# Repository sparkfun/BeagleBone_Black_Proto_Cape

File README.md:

BeagleBone Black Proto Cape
===========================

[
*BeagleBone Black Proto Cape (DEV-12774)*](https://www.sparkfun.com/products/12774)
 
 A prototyping cape designed for the BeagleBone Black. It has blank EEPROM for pin configuration data and
 two red LEDs for debugging. 

Repository Contents
-------------------
* **/Hardware** - All Eagle design files (.brd, .sch, .STL)
* **/Production** - Test bed files and production panel files

Version History
---------------
* [V_1.0.0](https://github.com/sparkfun/BeagleBone_Black_Proto_Cape/tree/V_1.0.0) - Public release
* [V_1.0.1](https://github.com/sparkfun/BeagleBone_Black_Proto_Cape/tree/V_1.0.1) - Updated jumper packages to DFM standard (Increased aperture).

License Information
-------------------
The hardware is released under [Creative Commons ShareAlike 4.0 International](https://creativecommons.org/licenses/by-sa/4.0/).
The code is beerware; if you see me (or any other SparkFun employee) at the local, and you've found our code helpful, please buy us a round!

Distributed as-is; no warranty is given.

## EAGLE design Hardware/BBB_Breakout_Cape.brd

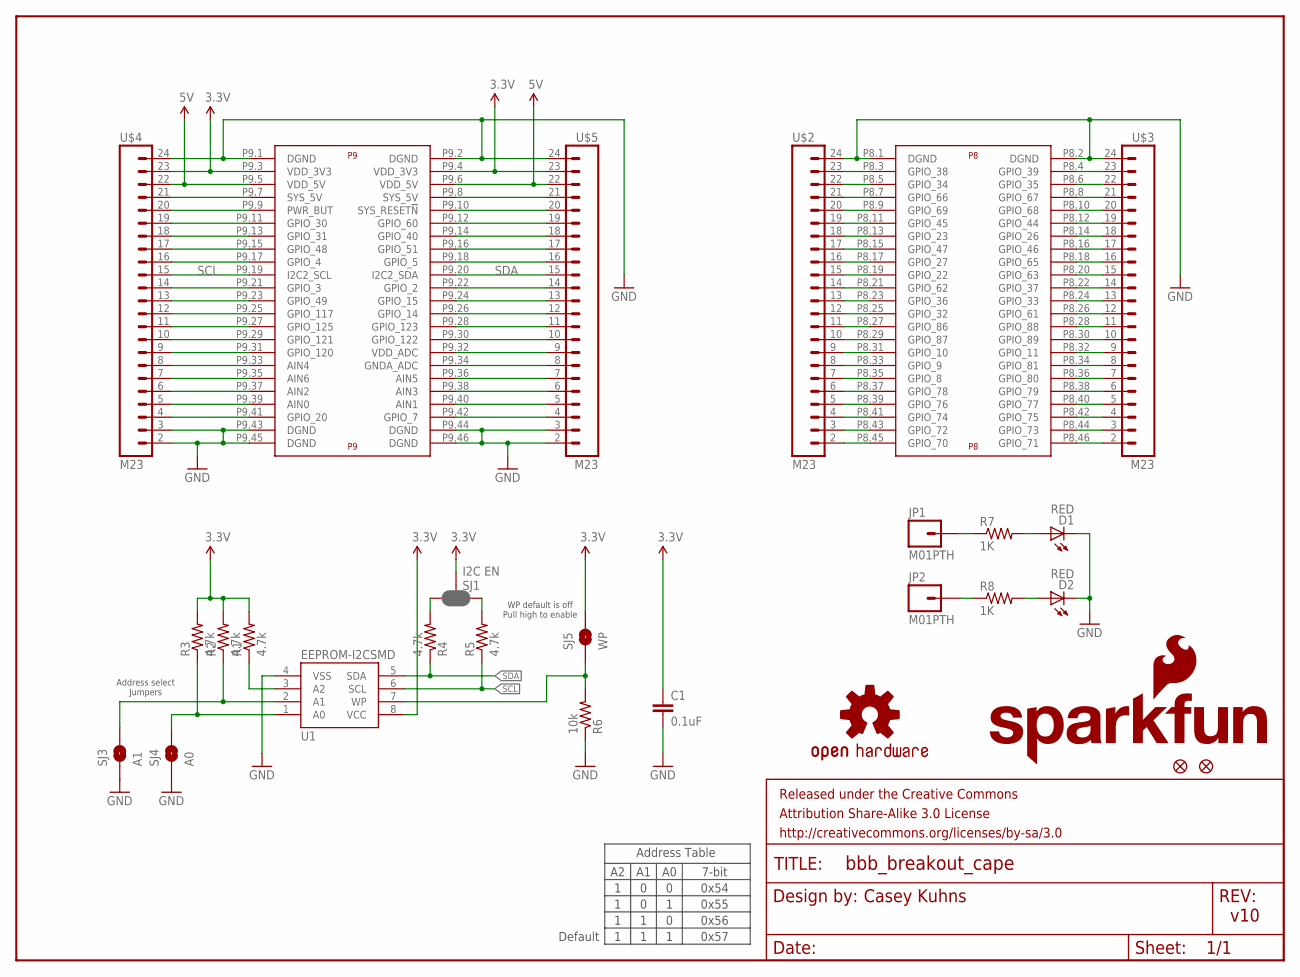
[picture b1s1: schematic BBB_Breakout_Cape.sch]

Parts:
C1: 0.1uF; 0603-CAP
D1, D2: RED; LED-0603
FID1, FID2: FIDUCIAL1X2; FIDUCIAL-1X2
FRAME1: FRAME-LETTER; CREATIVE_COMMONS
JP1, JP2: M01PTH; 1X01
LOGO2: OSHW-LOGOS; OSHW-LOGO-S
LOGO3: SFE_LOGO_NAME_FLAME.1_INCH; SFE_LOGO_NAME_FLAME_.1
R1, R2, R3, R4, R5: 4.7k; 0603@1
R6: 10k; 0603-RES
R7, R8: 1K; 0603-RES
SJ1: I2C EN; SMT-JUMPER_3_2-NC_PASTE_SILK
SJ3: A1; SMT-JUMPER_2_NO_SILK
SJ4: A0; SMT-JUMPER_2_NO_SILK
SJ5: WP; SMT-JUMPER_2_NO_SILK
U1: EEPROM-I2CSMD; SO08
U$1: BEAGLE_BONE_BLACK_CAPE
U$2, U$3, U$4, U$5: M23; 1X23

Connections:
3.3V: C1.1, R1.2, R2.2, R3.2, SJ1.2, SJ5.2, U1.8 (VCC), U$1.P9.3 (VDD_3V3), U$1.P9.4 (VDD_3V3), U$4.23, U$5.23
5V: U$1.P9.5 (VDD_5V), U$1.P9.6 (VDD_5V), U$4.22, U$5.22
A0: R3.1, SJ4.2, U1.1 (A0)
A1: R2.1, SJ3.2, U1.2 (A1)
GND: C1.2, D1.C, D2.C, R6.1, SJ3.1, SJ4.1, U1.4 (VSS), U$1.P8.1 (DGND), U$1.P8.2 (DGND), U$1.P9.1 (DGND), U$1.P9.2 (DGND), U$1.P9.43 (DGND), U$1.P9.44 (DGND), U$1.P9.45 (DGND), U$1.P9.46 (DGND), U$2.24, U$3.24, U$4.2, U$4.3, U$4.24, U$5.2, U$5.3, U$5.24
unnamed: R6.2, SJ5.1, U1.7 (WP)
unnamed: U$1.P8.45 (GPIO_70), U$2.2
unnamed: D1.A, R7.2
unnamed: U$1.P8.43 (GPIO_72), U$2.3
unnamed: U$1.P8.41 (GPIO_74), U$2.4
unnamed: R1.1, U1.3 (A2)
unnamed: D2.A, R8.2
unnamed: JP1.1, R7.1
unnamed: U$1.P8.39 (GPIO_76), U$2.5
unnamed: R4.2, SJ1.3
unnamed: R5.2, SJ1.1
unnamed: U$1.P8.37 (GPIO_78), U$2.6
unnamed: U$1.P8.35 (GPIO_8), U$2.7
unnamed: U$1.P8.33 (GPIO_9), U$2.8
unnamed: U$1.P8.31 (GPIO_10), U$2.9
unnamed: U$1.P8.29 (GPIO_87), U$2.10
unnamed: U$1.P8.27 (GPIO_86), U$2.11
unnamed: U$1.P8.25 (GPIO_32), U$2.12
unnamed: U$1.P8.23 (GPIO_36), U$2.13
unnamed: U$1.P8.21 (GPIO_62), U$2.14
unnamed: U$1.P8.19 (GPIO_22), U$2.15
unnamed: U$1.P8.17 (GPIO_27), U$2.16
unnamed: U$1.P8.15 (GPIO_47), U$2.17
unnamed: U$1.P8.13 (GPIO_23), U$2.18
unnamed: U$1.P8.11 (GPIO_45), U$2.19
unnamed: U$1.P8.9 (GPIO_69), U$2.20
unnamed: U$1.P8.7 (GPIO_66), U$2.21
unnamed: U$1.P8.5 (GPIO_34), U$2.22
unnamed: U$1.P8.3 (GPIO_38), U$2.23
unnamed: JP2.1, R8.1
unnamed: U$1.P8.46 (GPIO_71), U$3.2
unnamed: U$1.P8.44 (GPIO_73), U$3.3
unnamed: U$1.P8.42 (GPIO_75), U$3.4
unnamed: U$1.P8.40 (GPIO_77), U$3.5
unnamed: U$1.P8.38 (GPIO_79), U$3.6
unnamed: U$1.P8.36 (GPIO_80), U$3.7
unnamed: U$1.P8.34 (GPIO_81), U$3.8
unnamed: U$1.P8.32 (GPIO_11), U$3.9
unnamed: U$1.P8.30 (GPIO_89), U$3.10
unnamed: U$1.P8.28 (GPIO_88), U$3.11
unnamed: U$1.P8.26 (GPIO_61), U$3.12
unnamed: U$1.P8.24 (GPIO_33), U$3.13
unnamed: U$1.P8.22 (GPIO_37), U$3.14
unnamed: U$1.P8.20 (GPIO_63), U$3.15
unnamed: U$1.P8.18 (GPIO_65), U$3.16
unnamed: U$1.P8.16 (GPIO_46), U$3.17
unnamed: U$1.P8.14 (GPIO_26), U$3.18
unnamed: U$1.P8.12 (GPIO_44), U$3.19
unnamed: U$1.P8.10 (GPIO_68), U$3.20
unnamed: U$1.P8.8 (GPIO_67), U$3.21
unnamed: U$1.P8.6 (GPIO_35), U$3.22
unnamed: U$1.P8.4 (GPIO_39), U$3.23
unnamed: U$1.P9.42 (GPIO_7), U$5.4
unnamed: U$1.P9.40 (AIN1), U$5.5
unnamed: U$1.P9.38 (AIN3), U$5.6
unnamed: U$1.P9.36 (AIN5), U$5.7
unnamed: U$1.P9.34 (GNDA_ADC), U$5.8
unnamed: U$1.P9.32 (VDD_ADC), U$5.9
unnamed: U$1.P9.30 (GPIO_122), U$5.10
unnamed: U$1.P9.28 (GPIO_123), U$5.11
unnamed: U$1.P9.26 (GPIO_14), U$5.12
unnamed: U$1.P9.24 (GPIO_15), U$5.13
unnamed: U$1.P9.22 (GPIO_2), U$5.14
unnamed: U$1.P9.18 (GPIO_5), U$5.16
unnamed: U$1.P9.16 (GPIO_51), U$5.17
unnamed: U$1.P9.14 (GPIO_40), U$5.18
unnamed: U$1.P9.12 (GPIO_60), U$5.19
unnamed: U$1.P9.10 (SYS_RESET!N), U$5.20
unnamed: U$1.P9.8 (SYS_5V), U$5.21
unnamed: U$1.P9.41 (GPIO_20), U$4.4
unnamed: U$1.P9.39 (AIN0), U$4.5
unnamed: U$1.P9.37 (AIN2), U$4.6
unnamed: U$1.P9.35 (AIN6), U$4.7
unnamed: U$1.P9.33 (AIN4), U$4.8
unnamed: U$1.P9.31 (GPIO_120), U$4.9
unnamed: U$1.P9.29 (GPIO_121), U$4.10
unnamed: U$1.P9.27 (GPIO_125), U$4.11
unnamed: U$1.P9.25 (GPIO_117), U$4.12
unnamed: U$1.P9.23 (GPIO_49), U$4.13
unnamed: U$1.P9.21 (GPIO_3), U$4.14
unnamed: U$1.P9.17 (GPIO_4), U$4.16
unnamed: U$1.P9.15 (GPIO_48), U$4.17
unnamed: U$1.P9.13 (GPIO_31), U$4.18
unnamed: U$1.P9.11 (GPIO_30), U$4.19
unnamed: U$1.P9.9 (PWR_BUT), U$4.20
unnamed: U$1.P9.7 (SYS_5V), U$4.21
SCL: R5.1, U1.6 (SCL), U$1.P9.19 (I2C2_SCL), U$4.15
SDA: R4.1, U1.5 (SDA), U$1.P9.20 (I2C2_SDA), U$5.15

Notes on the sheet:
Address Table
Default
7-bit
0x54
0x56
0x55
0x57
Casey Kuhns
v10
WP default is off Pull high to enable
Address select Jumpers

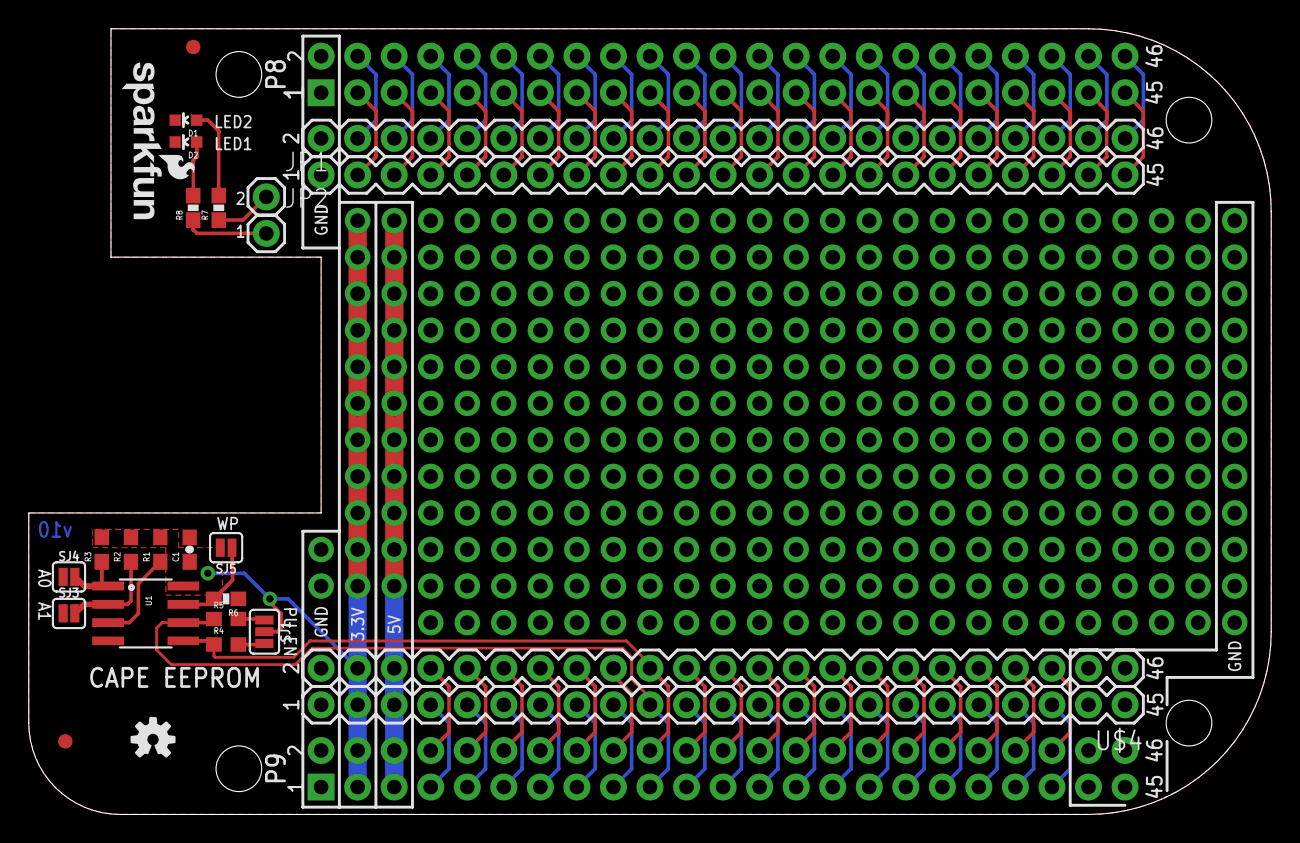
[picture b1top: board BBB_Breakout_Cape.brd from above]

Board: 2 copper layers, 86.4 x 54.6 mm, 29 parts (1 on the bottom side), 93 nets.

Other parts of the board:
U$6: SFE_LOGO_NAME_FLAME_.1

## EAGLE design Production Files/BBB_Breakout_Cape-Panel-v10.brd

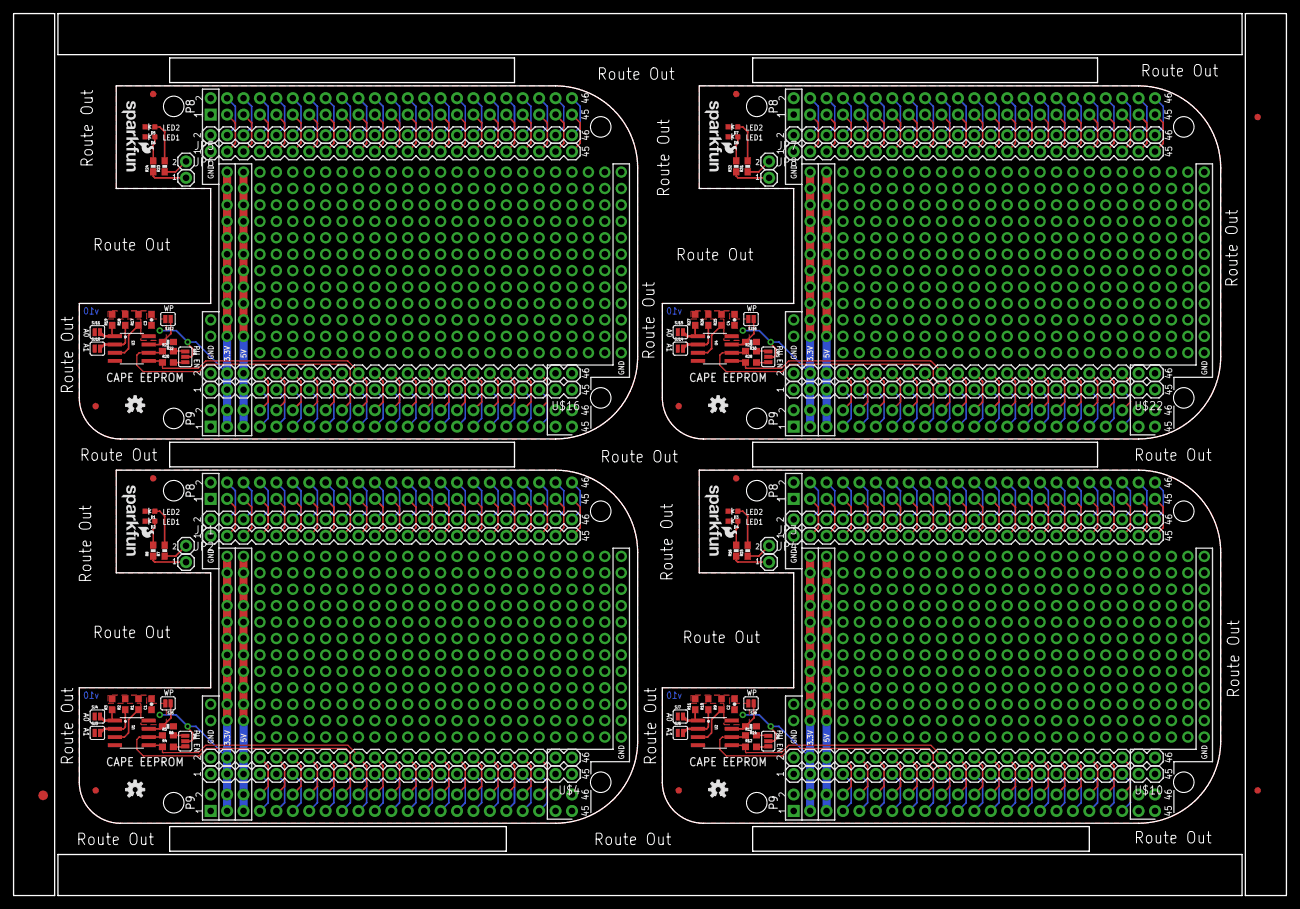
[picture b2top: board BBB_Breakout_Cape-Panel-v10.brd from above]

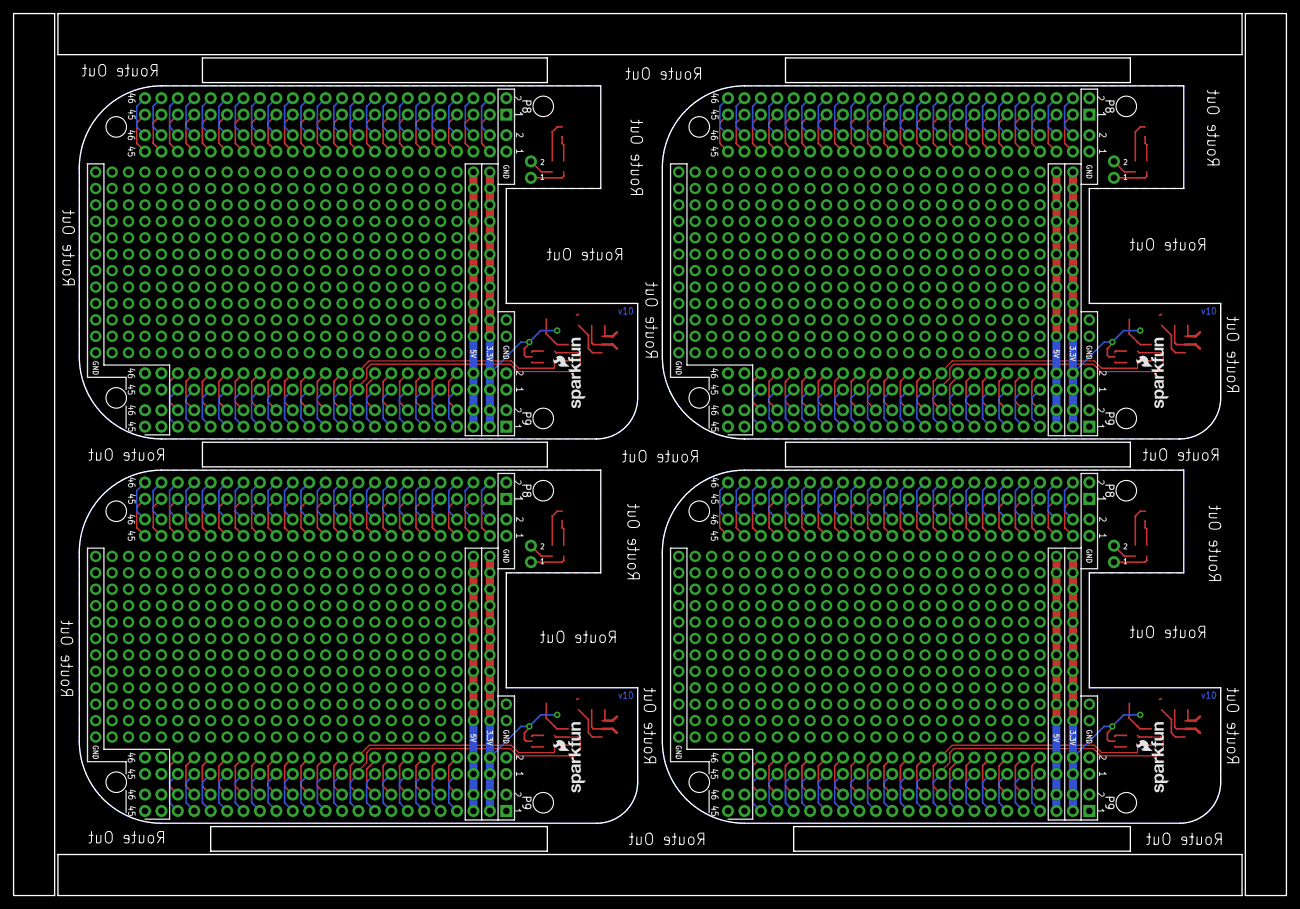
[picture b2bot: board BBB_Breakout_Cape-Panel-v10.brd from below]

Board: 2 copper layers, 196.8 x 136.4 mm, 115 parts (4 on the bottom side), 372 nets.

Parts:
C1, C2, C3, C4: 0.1uF; 0603-CAP
D1, D2, D3, D4, D5, D6, D7, D8: RED; LED-0603
E$1: FIDUCIAL-1.5X3
E$3, E$4: FIDUCIAL-1X2
FID1, FID2, FID3, FID4, FID5, FID6, FID7, FID8: FIDUCIAL1X2; FIDUCIAL-1X2
JP1, JP2, JP3, JP4, JP5, JP6, JP7, JP8: M01PTH; 1X01
LOGO1, LOGO3, LOGO5, LOGO7: SFE_LOGO_NAME_FLAME.1_INCH; SFE_LOGO_NAME_FLAME_.1
LOGO2, LOGO4, LOGO6, LOGO8: OSHW-LOGOS; OSHW-LOGO-S
R1, R2, R3, R4, R5, R9, R10, R11, R12, R13, R17, R18, R19, R20, R21, R25, R26, R27, R28, R29: 4.7k; 0603
R6, R14, R22, R30: 10k; 0603-RES
R7, R8, R15, R16, R23, R24, R31, R32: 1K; 0603-RES
SJ1, SJ2, SJ9, SJ13: I2C EN; SMT-JUMPER_3_2-NC_PASTE_SILK
SJ3, SJ6, SJ10, SJ14: A1; SMT-JUMPER_2_NO_SILK
SJ4, SJ7, SJ11, SJ15: A0; SMT-JUMPER_2_NO_SILK
SJ5, SJ8, SJ12, SJ16: WP; SMT-JUMPER_2_NO_SILK
U1, U2, U3, U4: EEPROM-I2CSMD; SO08
U$1, U$7, U$13, U$19: BEAGLE_BONE_BLACK_CAPE
U$2, U$3, U$4, U$5, U$8, U$9, U$10, U$11, U$14, U$15, U$16, U$17, U$20, U$21, U$22, U$23: M23; 1X23
U$6, U$12, U$18, U$24: SFE_LOGO_NAME_FLAME_.1

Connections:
3.3V: C1.1, R1.2, R2.2, R3.2, SJ1.2, SJ5.2, U1.8, U$1.P9.3, U$1.P9.4, U$4.23, U$5.23
3.3V1: C2.1, R9.2, R10.2, R11.2, SJ2.2, SJ8.2, U2.8, U$7.P9.3, U$7.P9.4, U$10.23, U$11.23
3.3V2: C3.1, R17.2, R18.2, R19.2, SJ9.2, SJ12.2, U3.8, U$13.P9.3, U$13.P9.4, U$16.23, U$17.23
3.3V3: C4.1, R25.2, R26.2, R27.2, SJ13.2, SJ16.2, U4.8, U$19.P9.3, U$19.P9.4, U$22.23, U$23.23
5V: U$1.P9.5, U$1.P9.6, U$4.22, U$5.22
5V1: U$7.P9.5, U$7.P9.6, U$10.22, U$11.22
5V2: U$13.P9.5, U$13.P9.6, U$16.22, U$17.22
5V3: U$19.P9.5, U$19.P9.6, U$22.22, U$23.22
A0: R3.1, SJ4.2, U1.1
A1: R2.1, SJ3.2, U1.2
A2: R10.1, SJ6.2, U2.2
A3: R11.1, SJ7.2, U2.1
A4: R18.1, SJ10.2, U3.2
A5: R19.1, SJ11.2, U3.1
A6: R26.1, SJ14.2, U4.2
A7: R27.1, SJ15.2, U4.1
GND: C1.2, D1.C, D2.C, R6.1, SJ3.1, SJ4.1, U1.4, U$1.P8.1, U$1.P8.2, U$1.P9.1, U$1.P9.2, U$1.P9.43, U$1.P9.44, U$1.P9.45, U$1.P9.46, U$2.24, U$3.24, U$4.2, U$4.3, U$4.24, U$5.2, U$5.3, U$5.24
GND1: C2.2, D3.C, D4.C, R14.1, SJ6.1, SJ7.1, U2.4, U$7.P8.1, U$7.P8.2, U$7.P9.1, U$7.P9.2, U$7.P9.43, U$7.P9.44, U$7.P9.45, U$7.P9.46, U$8.24, U$9.24, U$10.2, U$10.3, U$10.24, U$11.2, U$11.3, U$11.24
GND2: C3.2, D5.C, D6.C, R22.1, SJ10.1, SJ11.1, U3.4, U$13.P8.1, U$13.P8.2, U$13.P9.1, U$13.P9.2, U$13.P9.43, U$13.P9.44, U$13.P9.45, U$13.P9.46, U$14.24, U$15.24, U$16.2, U$16.3, U$16.24, U$17.2, U$17.3, U$17.24
GND3: C4.2, D7.C, D8.C, R30.1, SJ14.1, SJ15.1, U4.4, U$19.P8.1, U$19.P8.2, U$19.P9.1, U$19.P9.2, U$19.P9.43, U$19.P9.44, U$19.P9.45, U$19.P9.46, U$20.24, U$21.24, U$22.2, U$22.3, U$22.24, U$23.2, U$23.3, U$23.24
unnamed: R6.2, SJ5.1, U1.7
unnamed: U$1.P8.45, U$2.2
unnamed: D1.A, R7.2
unnamed: U$1.P8.43, U$2.3
unnamed: U$1.P8.41, U$2.4
unnamed: R1.1, U1.3
unnamed: D2.A, R8.2
unnamed: JP1.1, R7.1
unnamed: U$1.P8.39, U$2.5
unnamed: R4.2, SJ1.3
unnamed: R5.2, SJ1.1
unnamed: U$1.P8.37, U$2.6
unnamed: U$1.P8.35, U$2.7
unnamed: U$1.P8.33, U$2.8
unnamed: U$1.P8.31, U$2.9
unnamed: U$1.P8.29, U$2.10
unnamed: U$1.P8.27, U$2.11
unnamed: U$1.P8.25, U$2.12
unnamed: U$1.P8.23, U$2.13
unnamed: U$1.P8.21, U$2.14
unnamed: U$1.P8.19, U$2.15
unnamed: U$1.P8.17, U$2.16
unnamed: U$1.P8.15, U$2.17
unnamed: U$1.P8.13, U$2.18
unnamed: U$1.P8.11, U$2.19
unnamed: U$1.P8.9, U$2.20
unnamed: U$1.P8.7, U$2.21
unnamed: U$1.P8.5, U$2.22
unnamed: U$1.P8.3, U$2.23
unnamed: JP2.1, R8.1
unnamed: U$1.P8.46, U$3.2
unnamed: U$1.P8.44, U$3.3
unnamed: U$1.P8.42, U$3.4
unnamed: U$1.P8.40, U$3.5
unnamed: U$1.P8.38, U$3.6
unnamed: U$1.P8.36, U$3.7
unnamed: U$1.P8.34, U$3.8
unnamed: U$1.P8.32, U$3.9
unnamed: U$1.P8.30, U$3.10
unnamed: U$1.P8.28, U$3.11
unnamed: U$1.P8.26, U$3.12
unnamed: U$1.P8.24, U$3.13
unnamed: U$1.P8.22, U$3.14
unnamed: U$1.P8.20, U$3.15
unnamed: U$1.P8.18, U$3.16
unnamed: U$1.P8.16, U$3.17
unnamed: U$1.P8.14, U$3.18
unnamed: U$1.P8.12, U$3.19
unnamed: U$1.P8.10, U$3.20
unnamed: U$1.P8.8, U$3.21
unnamed: U$1.P8.6, U$3.22
unnamed: U$1.P8.4, U$3.23
unnamed: R9.1, U2.3
unnamed: R12.2, SJ2.3
unnamed: R13.2, SJ2.1
unnamed: U$1.P9.42, U$5.4
unnamed: U$1.P9.40, U$5.5
unnamed: U$1.P9.38, U$5.6
unnamed: U$1.P9.36, U$5.7
unnamed: U$1.P9.34, U$5.8
unnamed: U$1.P9.32, U$5.9
unnamed: U$1.P9.30, U$5.10
unnamed: U$1.P9.28, U$5.11
unnamed: U$1.P9.26, U$5.12
unnamed: U$1.P9.24, U$5.13
unnamed: U$1.P9.22, U$5.14
unnamed: U$7.P8.45, U$8.2
unnamed: U$1.P9.18, U$5.16
unnamed: U$1.P9.16, U$5.17
unnamed: U$1.P9.14, U$5.18
unnamed: U$1.P9.12, U$5.19
unnamed: U$1.P9.10, U$5.20
unnamed: U$1.P9.8, U$5.21
unnamed: U$7.P8.43, U$8.3
unnamed: U$7.P8.41, U$8.4
unnamed: U$7.P8.39, U$8.5
unnamed: U$7.P8.37, U$8.6
unnamed: U$7.P8.35, U$8.7
unnamed: U$1.P9.41, U$4.4
unnamed: U$1.P9.39, U$4.5
unnamed: U$1.P9.37, U$4.6
unnamed: U$1.P9.35, U$4.7
unnamed: U$1.P9.33, U$4.8
unnamed: U$1.P9.31, U$4.9
unnamed: U$1.P9.29, U$4.10
unnamed: U$1.P9.27, U$4.11
unnamed: U$1.P9.25, U$4.12
unnamed: U$1.P9.23, U$4.13
unnamed: U$1.P9.21, U$4.14
unnamed: U$7.P8.33, U$8.8
unnamed: U$1.P9.17, U$4.16
unnamed: U$1.P9.15, U$4.17
unnamed: U$1.P9.13, U$4.18
unnamed: U$1.P9.11, U$4.19
unnamed: U$1.P9.9, U$4.20
unnamed: U$1.P9.7, U$4.21
unnamed: U$7.P8.31, U$8.9
unnamed: U$7.P8.29, U$8.10
unnamed: U$7.P8.27, U$8.11
unnamed: U$7.P8.25, U$8.12
unnamed: U$7.P8.23, U$8.13
unnamed: U$7.P8.21, U$8.14
unnamed: U$7.P8.19, U$8.15
unnamed: U$7.P8.17, U$8.16
unnamed: U$7.P8.15, U$8.17
unnamed: U$7.P8.13, U$8.18
unnamed: U$7.P8.11, U$8.19
unnamed: U$7.P8.9, U$8.20
unnamed: U$7.P8.7, U$8.21
unnamed: U$7.P8.5, U$8.22
unnamed: U$7.P8.3, U$8.23
unnamed: U$7.P8.46, U$9.2
unnamed: U$7.P8.44, U$9.3
unnamed: U$7.P8.42, U$9.4
unnamed: U$7.P8.40, U$9.5
unnamed: U$7.P8.38, U$9.6
unnamed: U$7.P8.36, U$9.7
unnamed: U$7.P8.34, U$9.8
unnamed: U$7.P8.32, U$9.9
unnamed: U$7.P8.30, U$9.10
unnamed: U$7.P8.28, U$9.11
unnamed: U$7.P8.26, U$9.12
unnamed: U$7.P8.24, U$9.13
unnamed: U$7.P8.22, U$9.14
unnamed: U$7.P8.20, U$9.15
unnamed: U$7.P8.18, U$9.16
unnamed: U$7.P8.16, U$9.17
unnamed: U$7.P8.14, U$9.18
unnamed: U$7.P8.12, U$9.19
unnamed: U$7.P8.10, U$9.20
unnamed: U$7.P8.8, U$9.21
unnamed: U$7.P8.6, U$9.22
unnamed: U$7.P8.4, U$9.23
unnamed: U$7.P9.42, U$11.4
unnamed: U$7.P9.40, U$11.5
unnamed: U$7.P9.38, U$11.6
unnamed: U$7.P9.36, U$11.7
unnamed: U$7.P9.34, U$11.8
unnamed: U$7.P9.32, U$11.9
unnamed: U$7.P9.30, U$11.10
unnamed: U$7.P9.28, U$11.11
unnamed: U$7.P9.26, U$11.12
unnamed: U$7.P9.24, U$11.13
unnamed: U$7.P9.22, U$11.14
unnamed: U$7.P9.18, U$11.16
unnamed: U$7.P9.16, U$11.17
unnamed: U$7.P9.14, U$11.18
unnamed: U$7.P9.12, U$11.19
unnamed: U$7.P9.10, U$11.20
unnamed: U$7.P9.8, U$11.21
unnamed: U$7.P9.41, U$10.4
unnamed: U$7.P9.39, U$10.5
unnamed: U$7.P9.37, U$10.6
unnamed: U$7.P9.35, U$10.7
unnamed: U$7.P9.33, U$10.8
unnamed: U$7.P9.31, U$10.9
unnamed: U$7.P9.29, U$10.10
unnamed: U$7.P9.27, U$10.11
unnamed: U$7.P9.25, U$10.12
unnamed: U$7.P9.23, U$10.13
unnamed: U$7.P9.21, U$10.14
unnamed: U$7.P9.17, U$10.16
unnamed: U$7.P9.15, U$10.17
unnamed: U$7.P9.13, U$10.18
unnamed: U$7.P9.11, U$10.19
unnamed: U$7.P9.9, U$10.20
unnamed: U$7.P9.7, U$10.21
unnamed: R14.2, SJ8.1, U2.7
unnamed: D3.A, R15.2
unnamed: D4.A, R16.2
unnamed: JP3.1, R15.1
unnamed: JP4.1, R16.1
unnamed: R17.1, U3.3
unnamed: R20.2, SJ9.3
unnamed: R21.2, SJ9.1
unnamed: U$13.P8.45, U$14.2
unnamed: U$13.P8.43, U$14.3
unnamed: U$13.P8.41, U$14.4
unnamed: U$13.P8.39, U$14.5
unnamed: U$13.P8.37, U$14.6
unnamed: U$13.P8.35, U$14.7
unnamed: U$13.P8.33, U$14.8
unnamed: U$13.P8.31, U$14.9
unnamed: U$13.P8.29, U$14.10
unnamed: U$13.P8.27, U$14.11
unnamed: U$13.P8.25, U$14.12
unnamed: U$13.P8.23, U$14.13
unnamed: U$13.P8.21, U$14.14
unnamed: U$13.P8.19, U$14.15
unnamed: U$13.P8.17, U$14.16
unnamed: U$13.P8.15, U$14.17
unnamed: U$13.P8.13, U$14.18
unnamed: U$13.P8.11, U$14.19
unnamed: U$13.P8.9, U$14.20
unnamed: U$13.P8.7, U$14.21
unnamed: U$13.P8.5, U$14.22
unnamed: U$13.P8.3, U$14.23
unnamed: U$13.P8.46, U$15.2
unnamed: U$13.P8.44, U$15.3
unnamed: U$13.P8.42, U$15.4
unnamed: U$13.P8.40, U$15.5
unnamed: U$13.P8.38, U$15.6
unnamed: U$13.P8.36, U$15.7
unnamed: U$13.P8.34, U$15.8
unnamed: U$13.P8.32, U$15.9
unnamed: U$13.P8.30, U$15.10
unnamed: U$13.P8.28, U$15.11
unnamed: U$13.P8.26, U$15.12
unnamed: U$13.P8.24, U$15.13
unnamed: U$13.P8.22, U$15.14
unnamed: U$13.P8.20, U$15.15
unnamed: U$13.P8.18, U$15.16
unnamed: U$13.P8.16, U$15.17
unnamed: U$13.P8.14, U$15.18
unnamed: U$13.P8.12, U$15.19
unnamed: U$13.P8.10, U$15.20
unnamed: U$13.P8.8, U$15.21
unnamed: U$13.P8.6, U$15.22
unnamed: U$13.P8.4, U$15.23
unnamed: U$13.P9.42, U$17.4
unnamed: U$13.P9.40, U$17.5
unnamed: U$13.P9.38, U$17.6
unnamed: U$13.P9.36, U$17.7
unnamed: U$13.P9.34, U$17.8
unnamed: U$13.P9.32, U$17.9
unnamed: U$13.P9.30, U$17.10
unnamed: U$13.P9.28, U$17.11
unnamed: U$13.P9.26, U$17.12
unnamed: U$13.P9.24, U$17.13
unnamed: U$13.P9.22, U$17.14
unnamed: U$13.P9.18, U$17.16
unnamed: U$13.P9.16, U$17.17
unnamed: U$13.P9.14, U$17.18
unnamed: U$13.P9.12, U$17.19
unnamed: U$13.P9.10, U$17.20
unnamed: U$13.P9.8, U$17.21
unnamed: U$13.P9.41, U$16.4
unnamed: U$13.P9.39, U$16.5
unnamed: U$13.P9.37, U$16.6
unnamed: U$13.P9.35, U$16.7
unnamed: U$13.P9.33, U$16.8
unnamed: U$13.P9.31, U$16.9
unnamed: U$13.P9.29, U$16.10
unnamed: U$13.P9.27, U$16.11
unnamed: U$13.P9.25, U$16.12
unnamed: U$13.P9.23, U$16.13
unnamed: U$13.P9.21, U$16.14
unnamed: U$13.P9.17, U$16.16
unnamed: U$13.P9.15, U$16.17
unnamed: U$13.P9.13, U$16.18
unnamed: U$13.P9.11, U$16.19
unnamed: U$13.P9.9, U$16.20
unnamed: U$13.P9.7, U$16.21
unnamed: R22.2, SJ12.1, U3.7
unnamed: D5.A, R23.2
unnamed: D6.A, R24.2
unnamed: JP5.1, R23.1
unnamed: JP6.1, R24.1
unnamed: R25.1, U4.3
unnamed: R28.2, SJ13.3
unnamed: R29.2, SJ13.1
unnamed: U$19.P8.45, U$20.2
unnamed: U$19.P8.43, U$20.3
unnamed: U$19.P8.41, U$20.4
unnamed: U$19.P8.39, U$20.5
unnamed: U$19.P8.37, U$20.6
unnamed: U$19.P8.35, U$20.7
unnamed: U$19.P8.33, U$20.8
unnamed: U$19.P8.31, U$20.9
unnamed: U$19.P8.29, U$20.10
unnamed: U$19.P8.27, U$20.11
unnamed: U$19.P8.25, U$20.12
unnamed: U$19.P8.23, U$20.13
unnamed: U$19.P8.21, U$20.14
unnamed: U$19.P8.19, U$20.15
unnamed: U$19.P8.17, U$20.16
unnamed: U$19.P8.15, U$20.17
unnamed: U$19.P8.13, U$20.18
unnamed: U$19.P8.11, U$20.19
unnamed: U$19.P8.9, U$20.20
unnamed: U$19.P8.7, U$20.21
unnamed: U$19.P8.5, U$20.22
unnamed: U$19.P8.3, U$20.23
unnamed: U$19.P8.46, U$21.2
unnamed: U$19.P8.44, U$21.3
unnamed: U$19.P8.42, U$21.4
unnamed: U$19.P8.40, U$21.5
unnamed: U$19.P8.38, U$21.6
unnamed: U$19.P8.36, U$21.7
unnamed: U$19.P8.34, U$21.8
unnamed: U$19.P8.32, U$21.9
unnamed: U$19.P8.30, U$21.10
unnamed: U$19.P8.28, U$21.11
unnamed: U$19.P8.26, U$21.12
unnamed: U$19.P8.24, U$21.13
unnamed: U$19.P8.22, U$21.14
unnamed: U$19.P8.20, U$21.15
unnamed: U$19.P8.18, U$21.16
unnamed: U$19.P8.16, U$21.17
unnamed: U$19.P8.14, U$21.18
unnamed: U$19.P8.12, U$21.19
unnamed: U$19.P8.10, U$21.20
unnamed: U$19.P8.8, U$21.21
unnamed: U$19.P8.6, U$21.22
unnamed: U$19.P8.4, U$21.23
unnamed: U$19.P9.42, U$23.4
unnamed: U$19.P9.40, U$23.5
unnamed: U$19.P9.38, U$23.6
unnamed: U$19.P9.36, U$23.7
unnamed: U$19.P9.34, U$23.8
unnamed: U$19.P9.32, U$23.9
unnamed: U$19.P9.30, U$23.10
unnamed: U$19.P9.28, U$23.11
unnamed: U$19.P9.26, U$23.12
unnamed: U$19.P9.24, U$23.13
unnamed: U$19.P9.22, U$23.14
unnamed: U$19.P9.18, U$23.16
unnamed: U$19.P9.16, U$23.17
unnamed: U$19.P9.14, U$23.18
unnamed: U$19.P9.12, U$23.19
unnamed: U$19.P9.10, U$23.20
unnamed: U$19.P9.8, U$23.21
unnamed: U$19.P9.41, U$22.4
unnamed: U$19.P9.39, U$22.5
unnamed: U$19.P9.37, U$22.6
unnamed: U$19.P9.35, U$22.7
unnamed: U$19.P9.33, U$22.8
unnamed: U$19.P9.31, U$22.9
unnamed: U$19.P9.29, U$22.10
unnamed: U$19.P9.27, U$22.11
unnamed: U$19.P9.25, U$22.12
unnamed: U$19.P9.23, U$22.13
unnamed: U$19.P9.21, U$22.14
unnamed: U$19.P9.17, U$22.16
unnamed: U$19.P9.15, U$22.17
unnamed: U$19.P9.13, U$22.18
unnamed: U$19.P9.11, U$22.19
unnamed: U$19.P9.9, U$22.20
unnamed: U$19.P9.7, U$22.21
unnamed: R30.2, SJ16.1, U4.7
unnamed: D7.A, R31.2
unnamed: D8.A, R32.2
unnamed: JP7.1, R31.1
unnamed: JP8.1, R32.1
SCL: R5.1, U1.6, U$1.P9.19, U$4.15
SCL1: R13.1, U2.6, U$7.P9.19, U$10.15
SCL2: R21.1, U3.6, U$13.P9.19, U$16.15
SCL3: R29.1, U4.6, U$19.P9.19, U$22.15
SDA: R4.1, U1.5, U$1.P9.20, U$5.15
SDA1: R12.1, U2.5, U$7.P9.20, U$11.15
SDA2: R20.1, U3.5, U$13.P9.20, U$17.15
SDA3: R28.1, U4.5, U$19.P9.20, U$23.15

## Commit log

2014-01-07 Initial Board commit
2014-02-13 board ready for review
2014-02-14 Updated labels and corrected silk on bottom layer
2014-02-20 added labels and corrected WP jumper to eliminate possible short.
2014-03-04 Changed I2C EN to PU EN
2014-03-24 added LEDS
2014-03-24 added more labels and fixed drill hole
2014-03-24 added version number
2014-03-25 added local fiducials
2014-03-25 Created Panel v10
2014-05-22 Updating README with product information
2017-02-24 added tag link to readme
2017-02-24 Fixed link
2017-02-24 Updated juper packages on design and panel. This only effects tcream layer.

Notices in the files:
parts and their libraries:
SparkFun-Boards: Licensing: CC v3.0 Share-Alike You are welcome to use this library for commercial purposes.
SparkFun-Aesthetics: Released under the Creative Commons Attribution Share-Alike 3.0 License
SparkFun-Aesthetics: http://creativecommons.org/licenses/by-sa/3.0
